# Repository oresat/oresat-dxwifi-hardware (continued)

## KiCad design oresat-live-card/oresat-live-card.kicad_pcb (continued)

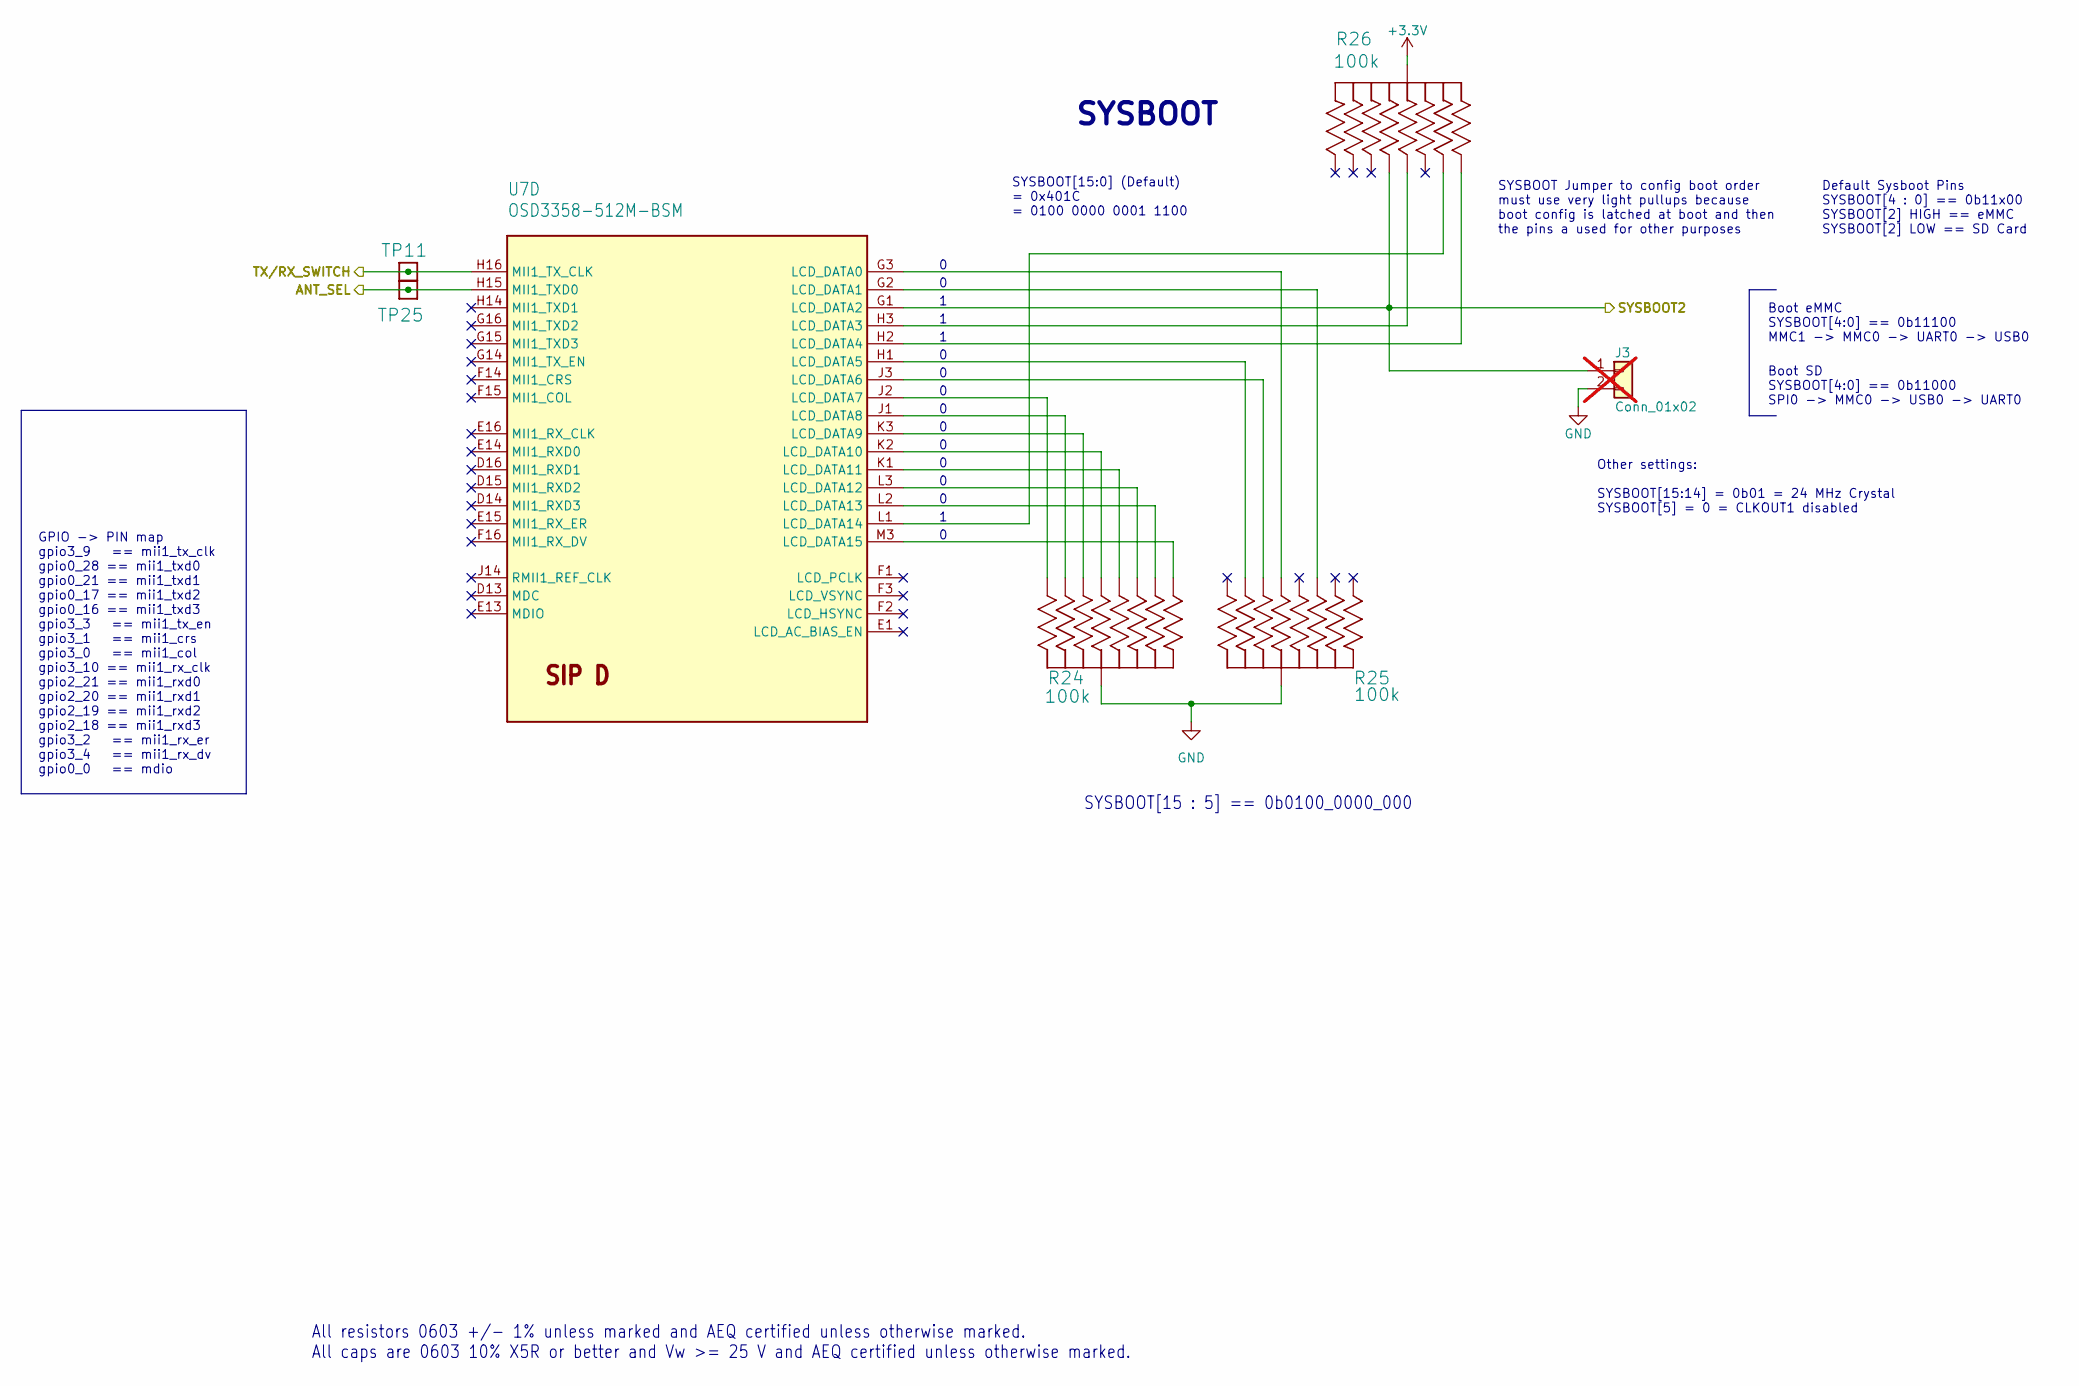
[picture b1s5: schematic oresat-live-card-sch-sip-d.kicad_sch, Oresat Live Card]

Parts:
J3: Conn_01x02; PinHeader_1x02_P2.54mm_Vertical; not fitted
R24, R25, R26: 100k; ARRAY_EXBA-M; MPN EXB-A10P104J
TP11, TP25: TEST-POINT3X4; TestPoint_Pad_D1.0mm
U7: OSD3358-512M-BSM; U-Octavo-OSD335X-BGA-256; MPN OSD3358-512M-BSM

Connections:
+3.3V: R26.5 (55), R26.10 (55); also elsewhere on the board
/Power + OPD/SYSBOOT2: J3.1, R26.8 (88), U7.G1 (LCD_DATA2); also elsewhere on the board
/SIP D: Boot/ANT_SEL: TP25.1 (1_1), U7.H15 (MII1_TXD0); also elsewhere on the board
/SIP D: Boot/TX/RX_SWITCH: TP11.1 (1_1), U7.H16 (MII1_TX_CLK); also elsewhere on the board
GND: J3.2, R24.5 (55), R24.10 (55), R25.5 (55), R25.10 (55); also elsewhere on the board
unnamed: R24.1 (11), U7.M3 (LCD_DATA15)
unnamed: R24.2 (22), U7.L3 (LCD_DATA12)
unnamed: R24.3 (33), U7.K2 (LCD_DATA10)
unnamed: R24.4 (44), U7.J1 (LCD_DATA8)
unnamed: R24.6 (66), U7.J2 (LCD_DATA7)
unnamed: R24.7 (77), U7.K3 (LCD_DATA9)
unnamed: R24.8 (88), U7.K1 (LCD_DATA11)
unnamed: R24.9 (99), U7.L2 (LCD_DATA13)
unnamed: R25.2 (22), U7.G2 (LCD_DATA1)
unnamed: R25.3 (33), U7.G3 (LCD_DATA0)
unnamed: R25.4 (44), U7.H1 (LCD_DATA5)
unnamed: R25.7 (77), U7.J3 (LCD_DATA6)
unnamed: R26.3 (33), U7.H3 (LCD_DATA3)
unnamed: R26.4 (44), U7.L1 (LCD_DATA14)
unnamed: R26.6 (66), U7.H2 (LCD_DATA4)

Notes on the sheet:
All resistors 0603 +/- 1% unless marked and AEQ certified unless otherwise marked. All caps are 0603 10% X5R or better and Vw >= 25 V and AEQ certified unless otherwise marked.
Boot eMMC SYSBOOT[4:0] == 0b11100 MMC1 -> MMC0 -> UART0 -> USB0
GPIO -> PIN map gpio3_9 == mii1_tx_clk gpio0_28 == mii1_txd0 gpio0_21 == mii1_txd1 gpio0_17 == mii1_txd2 gpio0_16 == mii1_txd3 gpio3_3 == mii1_tx_en gpio3_1 == mii1_crs gpio3_0 == mii1_col gpio3_10 == mii1_rx_clk gpio2_21 == mii1_rxd0 gpio2_20 == mii1_rxd1 gpio2_19 == mii1_rxd2 gpio2_18 == mii1_rxd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
Boot SD SYSBOOT[4:0] == 0b11000 SPI0 -> MMC0 -> USB0 -> UART0
SYSBOOT[15 : 5] == 0b0100_0000_000
SYSBOOT Jumper to config boot order must use very light pullups because boot config is latched at boot and then the pins a used for other purposes
Other settings: SYSBOOT[15:14] = 0b01 = 24 MHz Crystal SYSBOOT[5] = 0 = CLKOUT1 disabled
SYSBOOT
Default Sysboot Pins SYSBOOT[4 : 0] == 0b11x00 SYSBOOT[2] HIGH == eMMC SYSBOOT[2] LOW == SD Card
SYSBOOT[15:0] (Default) = 0x401C = 0100 0000 0001 1100

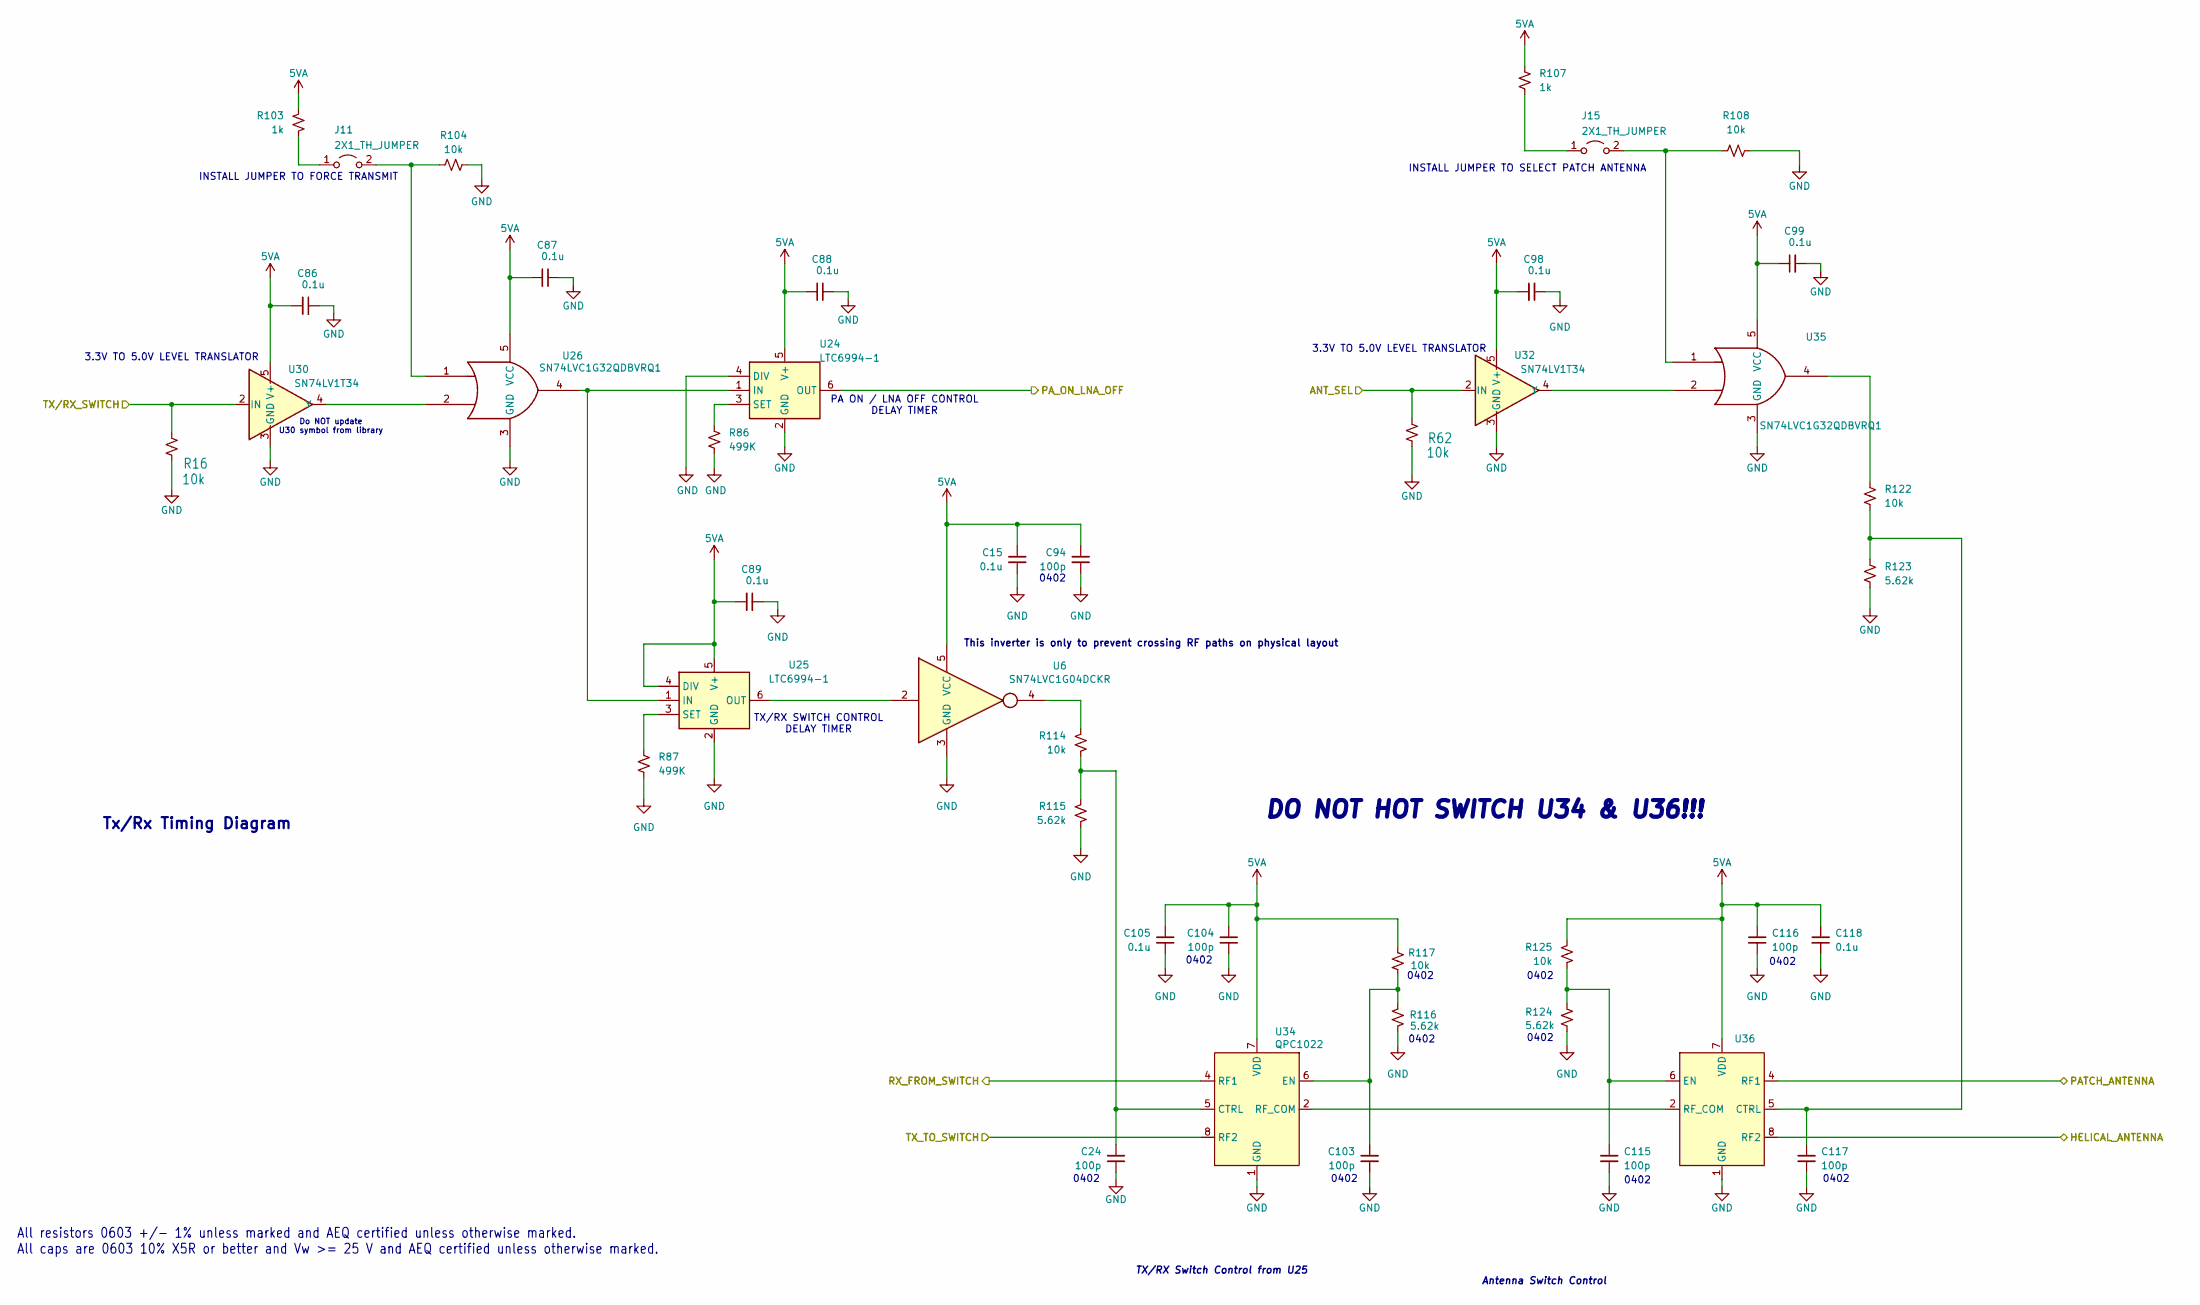
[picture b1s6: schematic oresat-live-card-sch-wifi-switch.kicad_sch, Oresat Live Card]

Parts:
C15, C86, C87, C88, C89, C98, C99, C105, C118: 0.1u; 0603-C-NOSILK; MPN C0603C104K5RACAUTO
C24, C94, C103, C104, C115, C116, C117: 100p; 0402-C-NOSILK; MPN GCM1555C1H101GA16D
J11, J15: 2X1_TH_JUMPER; 2X1; MPN XGL4020-332MEC
R16, R62, R104, R108, R114, R122: 10k; 0603-C-NOSILK; MPN RMCF0603FT10K0
R86, R87: 499K; 0603-C-NOSILK; MPN RMCF0603FT499K
R103, R107: 1k; 0603-C-NOSILK; MPN RMCF0603FT1K00
R115, R123: 5.62k; 0603-C-NOSILK; MPN RMCF0603FT5K62
R116, R124: 5.62k; 0402-C-NOSILK; MPN RMCF0402FT5K62
R117, R125: 10k; 0402-C-NOSILK; MPN RMCF0402FT10K0
U6: SN74LVC1G04DCKR; C70(TI-DCK); MPN SN74LVC1G04DCKR
U24, U25: LTC6994-1; TSOT-23-6; MPN LTC6994IS6-1#TRPBF
U26, U35: SN74LVC1G32QDBVRQ1; SOT-23-5; MPN SN74LVC1G32QDBVRQ1
U30, U32: SN74LV1T34; SOT-353_SC-70-5; MPN SN74LV1T34QDCKRQ1
U34, U36: QPC1022; MPN QPC1022TR7

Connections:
5VA: C15.1, C86.1, C87.1, C88.1, C89.1, C94.1, C98.1, C99.1, C104.1, C105.1, C116.1, C118.1, R103.1, R107.1, R117.1, R125.2, U6.5 (VCC), U24.5 (V+), U25.4 (DIV), U25.5 (V+), U26.5 (VCC), U30.5 (V+), U32.5 (V+), U34.7 (VDD), U35.5 (VCC), U36.7 (VDD); also elsewhere on the board
/HEL_ANT: U36.8 (RF2); also elsewhere on the board
/PATCH_ANT: U36.4 (RF1); also elsewhere on the board
/SIP D: Boot/ANT_SEL: R62.2, U32.2 (IN); also elsewhere on the board
/SIP D: Boot/TX/RX_SWITCH: R16.2, U30.2 (IN); also elsewhere on the board
/WiFi LNA/LNA_SHUTDOWN: U24.6 (OUT); also elsewhere on the board
/WiFi LNA/RX_FROM_SWITCH: U34.4 (RF1); also elsewhere on the board
/WiFi PA/TX_TO_SWITCH: U34.8 (RF2); also elsewhere on the board
GND: C15.2, C24.2, C86.2, C87.2, C88.2, C89.2, C94.2, C98.2, C99.2, C103.2, C104.2, C105.2, C115.2, C116.2, C117.2, C118.2, R16.1, R62.1, R86.2, R87.2, R104.2, R108.2, R115.2, R116.2, R123.1, R124.1, U6.3 (GND), U24.2 (GND), U24.4 (DIV), U25.2 (GND), U26.3 (GND), U30.3 (GND), U32.3 (GND), U34.1 (GND), U34.3 (GND), U34.9 (GND), U35.3 (GND), U36.1 (GND), U36.3 (GND), U36.9 (GND); also elsewhere on the board
unnamed: J11.1 (A), R103.2
unnamed: J11.2 (B), R104.1, U26.1
unnamed: J15.1 (A), R107.2
unnamed: J15.2 (B), R108.1, U35.1
unnamed: R114.2, U6.4
unnamed: R122.1, U35.4
unnamed: U24.1 (IN), U25.1 (IN), U26.4
unnamed: R86.1, U24.3 (SET)
unnamed: U6.2, U25.6 (OUT)
unnamed: R87.1, U25.3 (SET)
unnamed: U26.2, U30.4 (Y)
unnamed: U32.4 (Y), U35.2
unnamed: C24.1, R114.1, R115.1, U34.5 (CTRL)
unnamed: C103.1, R116.1, R117.2, U34.6 (EN)
unnamed: U34.2 (RF_COM), U36.2 (RF_COM)
unnamed: C117.1, R122.2, R123.2, U36.5 (CTRL)
unnamed: C115.1, R124.2, R125.1, U36.6 (EN)

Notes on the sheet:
DO NOT HOT SWITCH U34 & U36!!!
3.3V TO 5.0V LEVEL TRANSLATOR
0402
This inverter is only to prevent crossing RF paths on physical layout
Tx/Rx Timing Diagram
INSTALL JUMPER TO SELECT PATCH ANTENNA
Do NOT update U30 symbol from library
TX/RX SWITCH CONTROL DELAY TIMER
All resistors 0603 +/- 1% unless marked and AEQ certified unless otherwise marked. All caps are 0603 10% X5R or better and Vw >= 25 V and AEQ certified unless otherwise marked.
Antenna Switch Control
PA ON / LNA OFF CONTROL DELAY TIMER
INSTALL JUMPER TO FORCE TRANSMIT
3.3V TO 5.0V LEVEL TRANSLATOR
TX/RX Switch Control from U25

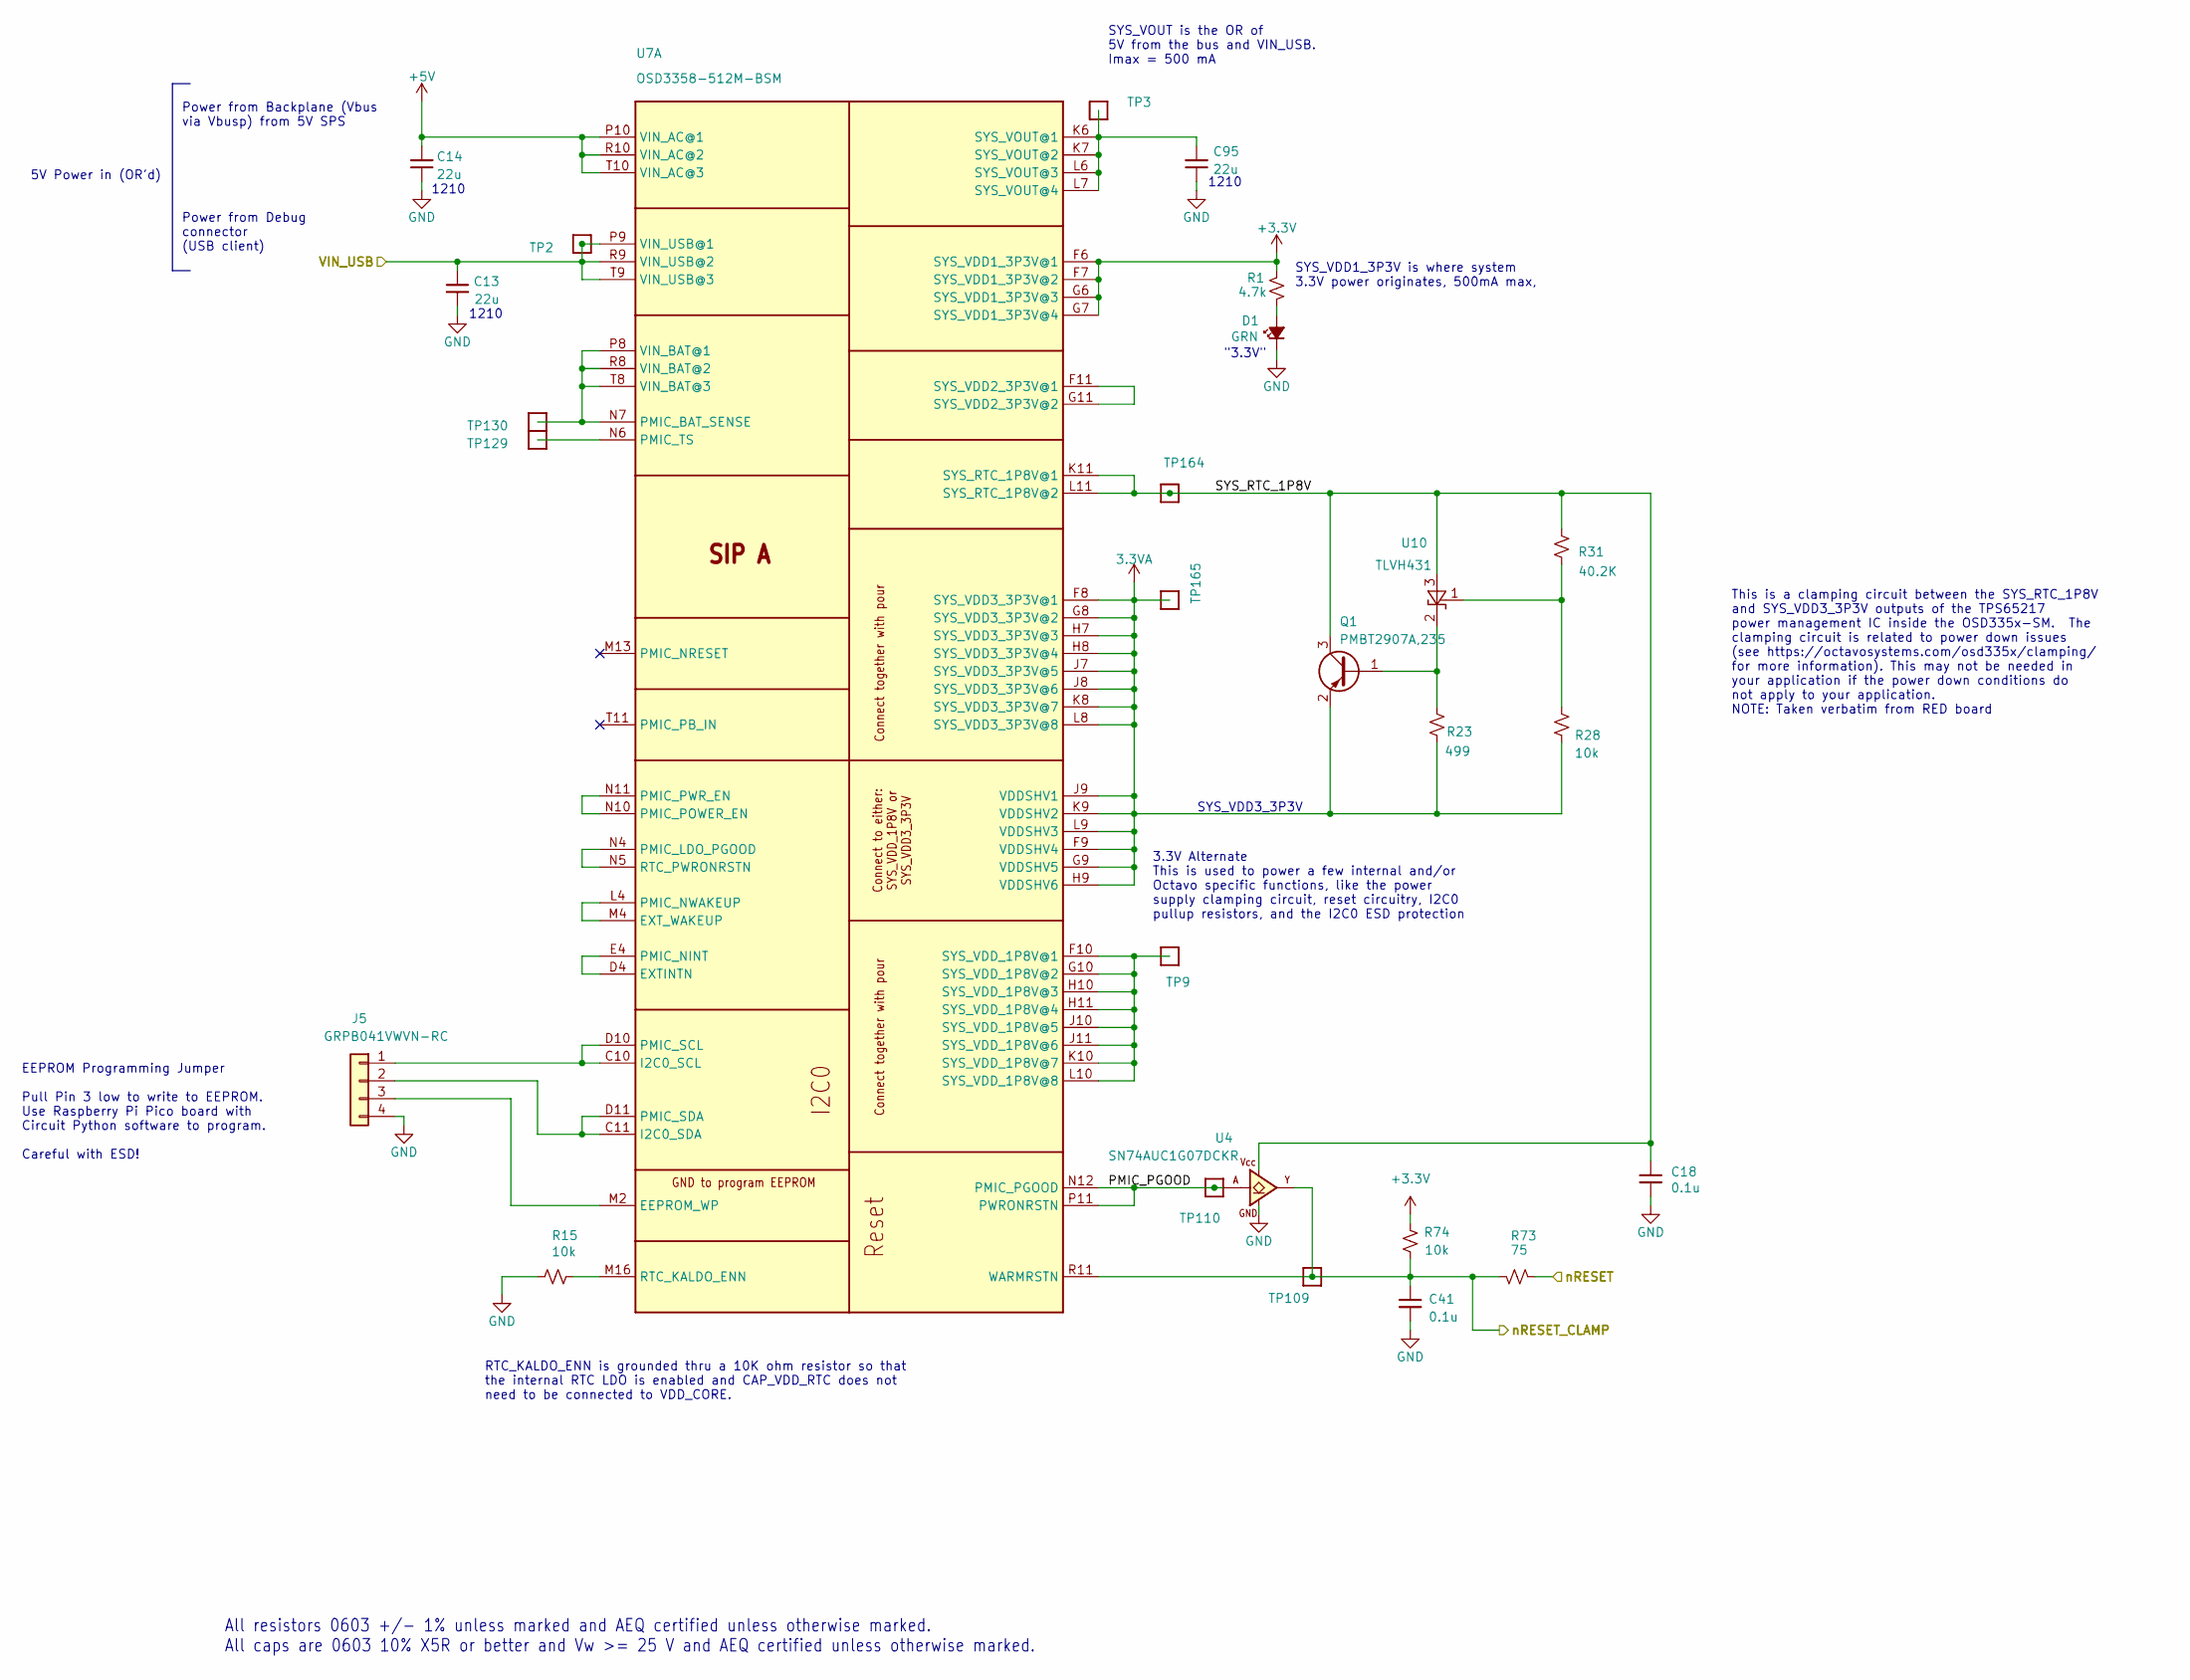
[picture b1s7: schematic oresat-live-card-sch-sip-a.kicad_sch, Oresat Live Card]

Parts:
C13, C14, C95: 22u; C_1210_3225Metric; MPN TMK325B7226KMHP
C18, C41: 0.1u; 0603-C-NOSILK; MPN C0603C104K5RACAUTO
D1: GRN; LED-0603; MPN 150060GS75000
J5: GRPB041VWVN-RC; PinHeader_1x04_P1.27mm_Vertical; MPN GRPB041VWVN-RC
Q1: PMBT2907A,235; SOT-23; MPN PMBT2907A,235
R1: 4.7k; 0603-C-NOSILK; MPN RMCF0603FT4K70
R15, R28, R74: 10k; 0603-C-NOSILK; MPN RMCF0603FT10K0
R23: 499; 0603-C-NOSILK; MPN RMCF0603FT499R
R31: 40.2K; 0603-C-NOSILK; MPN RMCF0603FG40K2
R73: 75; 0603-C-NOSILK; MPN RMCF0603FT75R0
TP2, TP3, TP9, TP109, TP110, TP129, TP130, TP164, TP165: TEST-POINT3X4; TestPoint_Pad_D1.0mm
U4: SN74AUC1G07DCKR; C70(TI-DCK); MPN SN74AUC1G07DCKR
U7: OSD3358-512M-BSM; U-Octavo-OSD335X-BGA-256; MPN OSD3358-512M-BSM
U10: TLVH431; SOT23-3; MPN TLVH431BQDBZRQ1

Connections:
3.3VA: Q1.2 (E), R23.2, R28.2, TP165.1 (1_1), U7.F8 (SYS_VDD3_3P3V@1), U7.F9 (VDDSHV4), U7.G8 (SYS_VDD3_3P3V@2), U7.G9 (VDDSHV5), U7.H7 (SYS_VDD3_3P3V@3), U7.H8 (SYS_VDD3_3P3V@4), U7.H9 (VDDSHV6), U7.J7 (SYS_VDD3_3P3V@5), U7.J8 (SYS_VDD3_3P3V@6), U7.J9 (VDDSHV1), U7.K8 (SYS_VDD3_3P3V@7), U7.K9 (VDDSHV2), U7.L8 (SYS_VDD3_3P3V@8), U7.L9 (VDDSHV3)
+3.3V: R1.1, R74.2, U7.F6 (SYS_VDD1_3P3V@1), U7.F7 (SYS_VDD1_3P3V@2), U7.G6 (SYS_VDD1_3P3V@3), U7.G7 (SYS_VDD1_3P3V@4); also elsewhere on the board
+5V: C14.1, U7.P10 (VIN_AC@1), U7.R10 (VIN_AC@2), U7.T10 (VIN_AC@3); also elsewhere on the board
/SIP A: Power/PMIC_PGOOD: TP110.1 (1_1), U4.2 (A), U7.N12 (PMIC_PGOOD), U7.P11 (PWRONRSTN)
/SIP A: Power/SYS_RTC_1P8V: C18.1, Q1.3 (C), R31.1, TP164.1 (1_1), U4.5 (VCC), U7.K11 (SYS_RTC_1P8V@1), U7.L11 (SYS_RTC_1P8V@2), U10.3 (A)
/SIP A: Power/VIN_USB: C13.1, TP2.1 (1_1), U7.P9 (VIN_USB@1), U7.R9 (VIN_USB@2), U7.T9 (VIN_USB@3); also elsewhere on the board
/SIP A: Power/nRESET_CLAMP: C41.1, R73.2, R74.1, TP109.1 (1_1), U4.4 (Y), U7.R11 (WARMRSTN); also elsewhere on the board
/nRESET: R73.1; also elsewhere on the board
GND: C13.2, C14.2, C18.2, C41.2, C95.2, D1.1 (K), J5.4, R15.1, U4.3 (GND); also elsewhere on the board
unnamed: D1.2 (A), R1.2
unnamed: J5.1, U7.C10 (I2C0_SCL), U7.D10 (PMIC_SCL)
unnamed: J5.2, U7.C11 (I2C0_SDA), U7.D11 (PMIC_SDA)
unnamed: J5.3, U7.M2 (EEPROM_WP)
unnamed: Q1.1 (B), R23.1, U10.2 (K)
unnamed: U7.D4 (EXTINTN), U7.E4 (PMIC_NINT)
unnamed: U7.L4 (PMIC_NWAKEUP), U7.M4 (EXT_WAKEUP)
unnamed: TP130.1 (1_1), U7.N7 (PMIC_BAT_SENSE), U7.P8 (VIN_BAT@1), U7.R8 (VIN_BAT@2), U7.T8 (VIN_BAT@3)
unnamed: U7.N4 (PMIC_LDO_PGOOD), U7.N5 (RTC_PWRONRSTN)
unnamed: U7.N10 (PMIC_POWER_EN), U7.N11 (PMIC_PWR_EN)
unnamed: TP129.1 (1_1), U7.N6 (PMIC_TS)
unnamed: R15.2, U7.M16 (RTC_KALDO_ENN)
unnamed: U7.F11 (SYS_VDD2_3P3V@1), U7.G11 (SYS_VDD2_3P3V@2)
unnamed: TP9.1 (1_1), U7.F10 (SYS_VDD_1P8V@1), U7.G10 (SYS_VDD_1P8V@2), U7.H10 (SYS_VDD_1P8V@3), U7.H11 (SYS_VDD_1P8V@4), U7.J10 (SYS_VDD_1P8V@5), U7.J11 (SYS_VDD_1P8V@6), U7.K10 (SYS_VDD_1P8V@7), U7.L10 (SYS_VDD_1P8V@8)
unnamed: C95.1, TP3.1 (1_1), U7.K6 (SYS_VOUT@1), U7.K7 (SYS_VOUT@2), U7.L6 (SYS_VOUT@3), U7.L7 (SYS_VOUT@4)
unnamed: R28.1, R31.2, U10.1 (REF)

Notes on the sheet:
Power from Backplane (Vbus via Vbusp) from 5V SPS
All resistors 0603 +/- 1% unless marked and AEQ certified unless otherwise marked. All caps are 0603 10% X5R or better and Vw >= 25 V and AEQ certified unless otherwise marked.
SYS_VOUT is the OR of 5V from the bus and VIN_USB. Imax = 500 mA
EEPROM Programming Jumper Pull Pin 3 low to write to EEPROM. Use Raspberry Pi Pico board with Circuit Python software to program. Careful with ESD!
"3.3V"
5V Power in (OR'd)
RTC_KALDO_ENN is grounded thru a 10K ohm resistor so that the internal RTC LDO is enabled and CAP_VDD_RTC does not need to be connected to VDD_CORE.
SYS_VDD1_3P3V is where system 3.3V power originates, 500mA max,
Power from Debug connector (USB client)
This is a clamping circuit between the SYS_RTC_1P8V and SYS_VDD3_3P3V outputs of the TPS65217 power management IC inside the OSD335x-SM. The clamping circuit is related to power down issues (see https://octavosystems.com/osd335x/clamping/ for more information). This may not be needed in your applic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
1210
SYS_VDD3_3P3V
3.3V Alternate This is used to power a few internal and/or Octavo specific functions, like the power supply clamping circuit, reset circuitry, I2C0 pullup resistors, and the I2C0 ESD protection

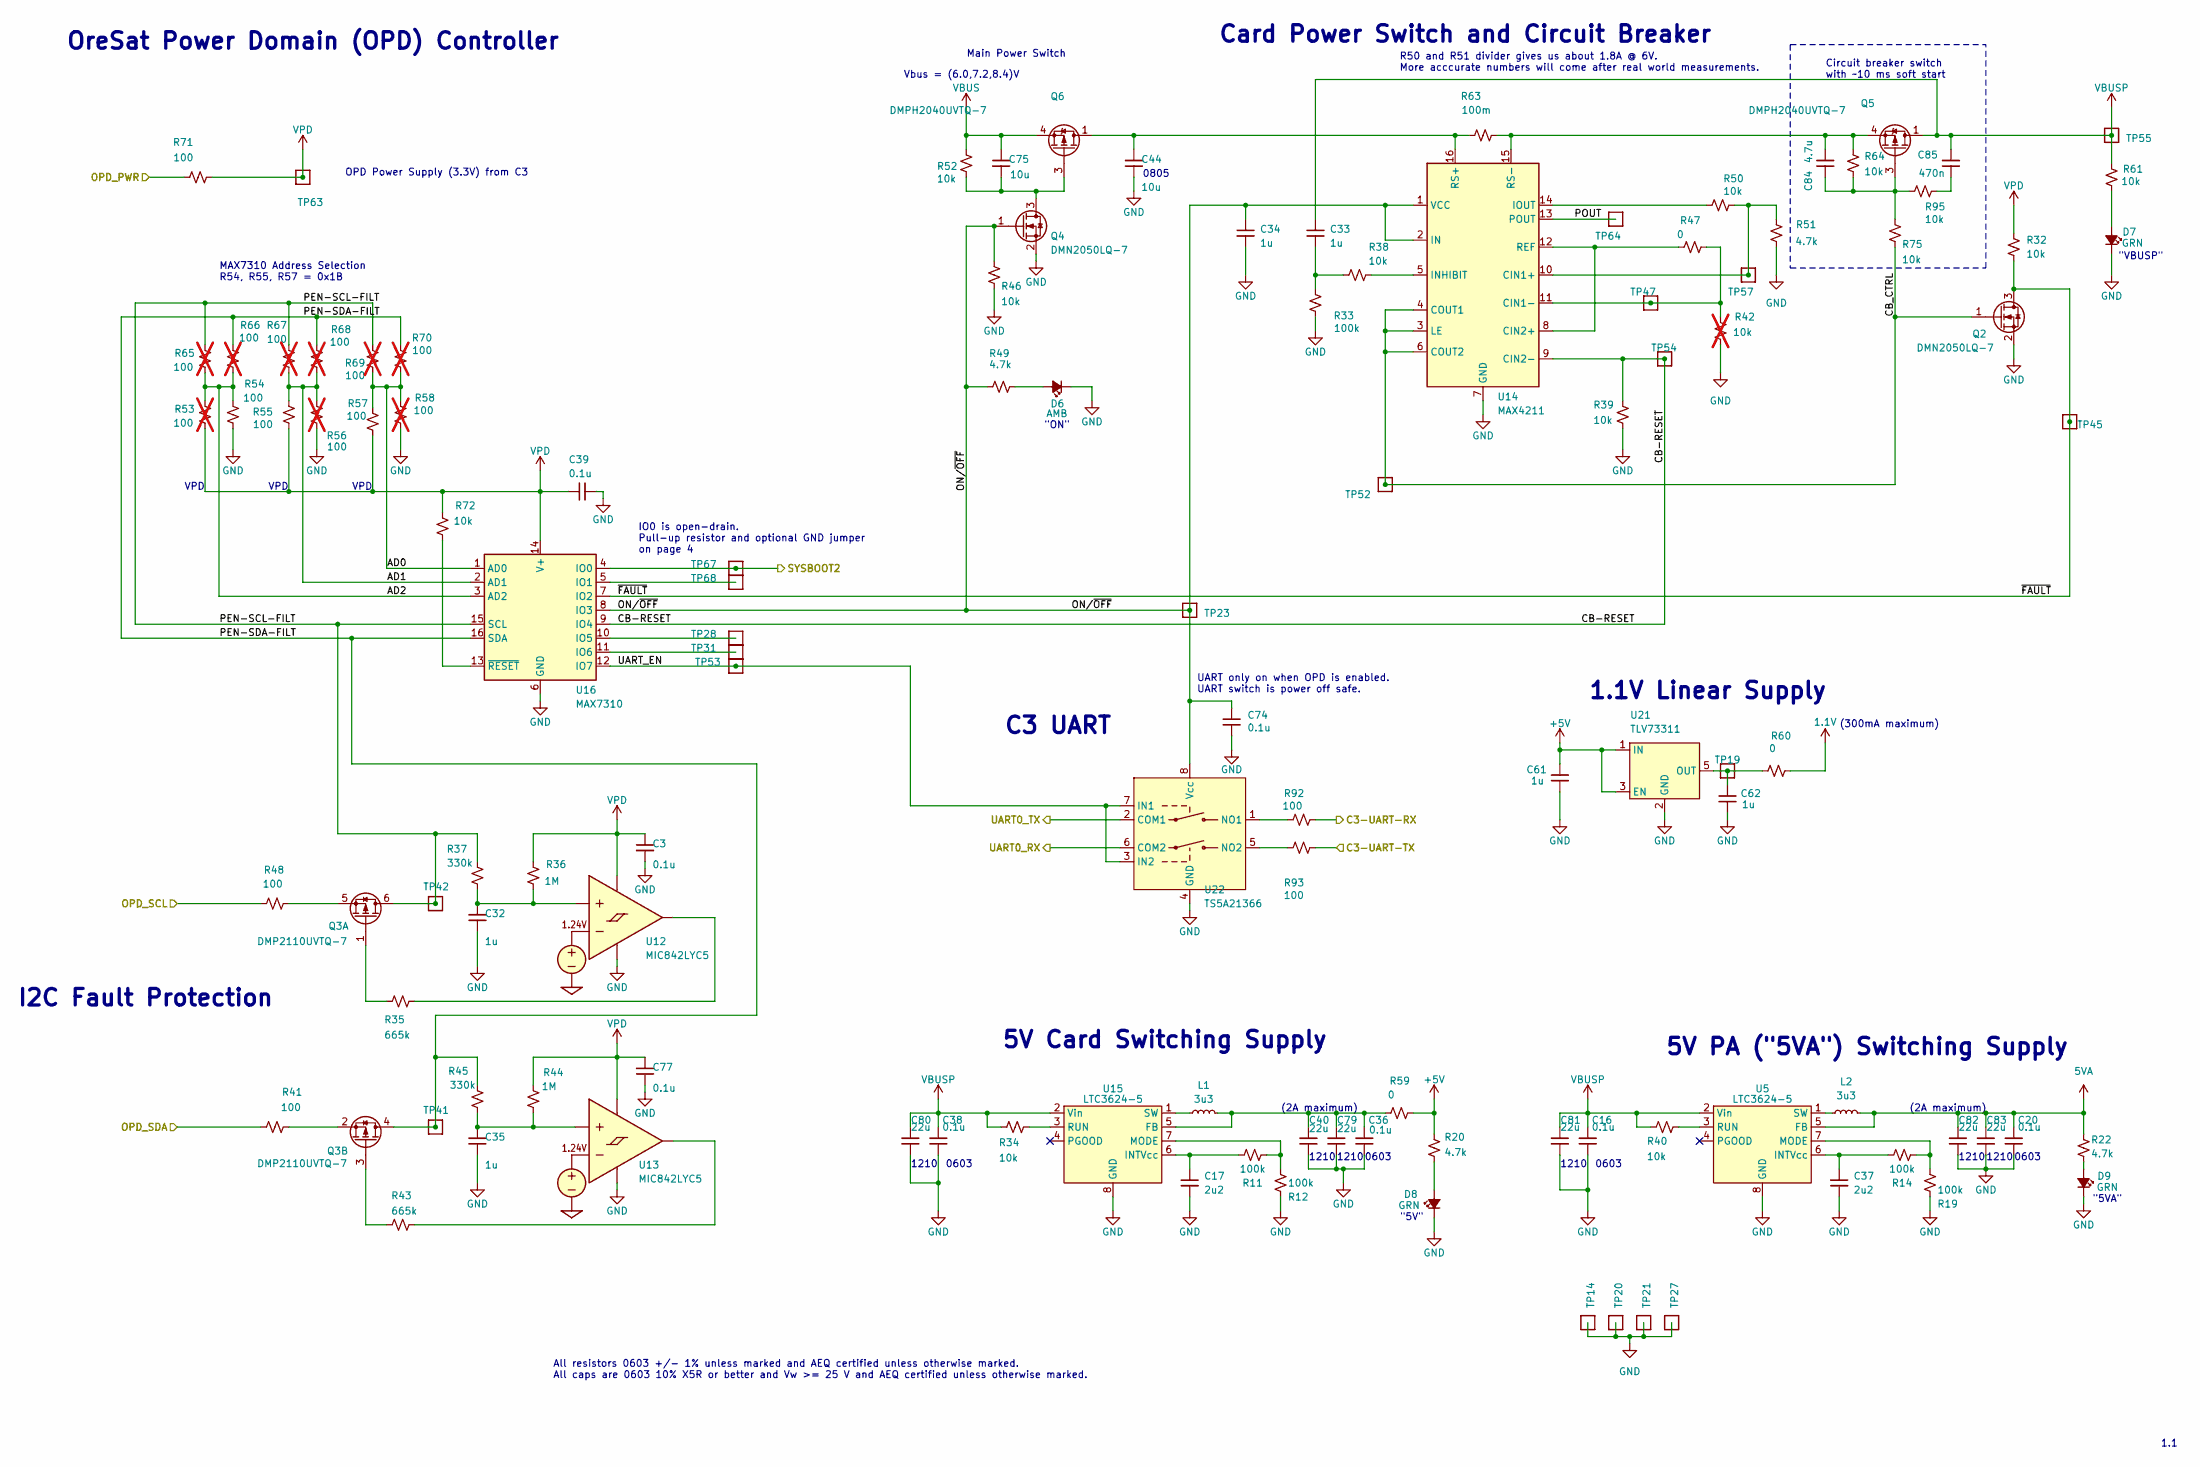
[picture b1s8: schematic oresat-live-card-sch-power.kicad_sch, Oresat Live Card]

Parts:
C3, C16, C20, C36, C38, C39, C74, C77: 0.1u; 0603-C-NOSILK; MPN C0603C104K5RACAUTO
C17, C37: 2u2; 0603-C-NOSILK; MPN GRT188C71E225KE13D
C32, C35: 1u; 0805-C-NOSILK; MPN GCM21BR71H105KA03L
C33, C34, C61, C62: 1u; 0603-C-NOSILK; MPN GRT188R71E105KE13D
C40, C79, C80, C81, C82, C83: 22u; C_1210_3225Metric; MPN TMK325B7226KMHP
C44, C75: 10u; 0805-C-NOSILK; MPN GRT21BC71E106KE13K
C84: 4.7u; 0805-C-NOSILK; MPN GRT21BC71E475KE13L
C85: 470n; 0603-C-NOSILK; MPN C0603C474K3RACAUTO
D6: AMB; LED-0603; MPN 150060AS75000
D7, D8, D9: GRN; LED-0603; MPN 150060GS75000
L1, L2: 3u3; L_Coilcraft_XxL4020; MPN XGL4020-332MEC
Q2, Q4: DMN2050LQ-7; SOT-23; MPN DMN2050LQ-7
Q3: DMP2110UVTQ-7; SOT-23-6; MPN DMP2110UVTQ-7
Q5, Q6: DMPH2040UVTQ-7; TSOT-23-6; MPN DMPH2040UVTQ-7
R11, R12, R14, R19, R33: 100k; 0603-C-NOSILK; MPN RMCF0603FT100K
R20, R22, R49, R51: 4.7k; 0603-C-NOSILK; MPN RMCF0603FT4K70
R32, R34, R38, R39, R40, R46, R50, R52, R61, R64, R72, R75, R95: 10k; 0603-C-NOSILK; MPN RMCF0603FT10K0
R35, R43: 665k; 0603-C-NOSILK; MPN RMCF0603FT665K
R36, R44: 1M; 0603-C-NOSILK; MPN RMCF0603FT1M00
R37, R45: 330k; 0603-C-NOSILK; MPN RMCF0603FT330K
R41, R48, R54, R55, R57, R71, R92, R93: 100; 0603-C-NOSILK; MPN RMCF0603FT100R
R42: 10k; R_0603_1608Metric; MPN ERJ-3EKF1002V; not fitted
R47, R59, R60: 0; 0603-C-NOSILK; MPN RMCF0603ZT0R00
R53, R56, R58, R65, R66, R67, R68, R69, R70: 100; 0603-C-NOSILK; MPN ERJ-3EKF1000V; not fitted
R63: 100m; 1206-C; MPN CSR1206FKR100
TP14, TP20, TP21, TP27, TP55: TEST-POINT; TestPoint-0.75mm-th
TP19, TP23, TP28, TP31, TP41, TP42, TP45, TP47, TP52, TP53, TP54, TP57, TP63, TP64, TP67, TP68: TEST-POINT; TestPoint_Pad_D1.0mm
U5, U15: LTC3624-5; DFN-8-1EP_3x3mm_P0.5mm_EP1.65x2.38mm_ThermalVias0.3mm; MPN LTC3624IDD-5#PBF
U12, U13: MIC842LYC5; SOT-353_SC-70-5; MPN MIC842LYC5-TR
U14: MAX4211; QFN-16-1EP_4x4mm_P0.65mm_EP2.1x2.1mm; MPN MAX4211FETE+
U16: MAX7310; QFN-16-1EP_4x4mm_P0.65mm_EP2.1x2.1mm; MPN MAX7310ATE+
U21: TLV73311; SOT-23-5; MPN TLV73311PDBVR
U22: TS5A21366; VSSOP-8_2.3x2mm_P0.5mm; MPN TS5A21366DCUR

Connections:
1.1V: R60.2; also elsewhere on the board
5VA: C20.1, C82.1, C83.1, L2.2, R22.1, U5.5 (FB); also elsewhere on the board
+5V: C61.1, R20.1, R59.2, U21.1 (IN), U21.3 (EN); also elsewhere on the board
/C3-UART-RX: R92.1; also elsewhere on the board
/C3-UART-TX: R93.1; also elsewhere on the board
/OPD_PWR: R71.1; also elsewhere on the board
/OPD_SCL: R48.1; also elsewhere on the board
/OPD_SDA: R41.1; also elsewhere on the board
/Power + OPD/AD0: R57.1, R58.2, R69.2, R70.1, U16.1 (AD0)
/Power + OPD/AD1: R55.1, R56.2, R67.2, R68.1, U16.2 (AD1)
/Power + OPD/AD2: R53.1, R54.2, R65.2, R66.1, U16.3 (AD2)
/Power + OPD/CB-RESET: R39.2, TP54.1 (1_1), U14.9 (CIN2-), U16.9 (IO4)
/Power + OPD/CB_CTRL: Q2.1 (G), R75.1, TP52.1 (1_1), U14.3 (LE), U14.4 (COUT1), U14.6 (COUT2)
/Power + OPD/ON/~OFF: C34.1, C74.1, Q4.1 (G), R46.2, R49.2, TP23.1 (1_1), U14.1 (VCC), U14.2 (IN), U16.8 (IO3), U22.8 (Vcc)
/Power + OPD/PEN-SCL-FILT: Q3.6 (D), R37.2, R65.1, R67.1, R69.1, TP42.1 (1_1), U16.15 (SCL)
/Power + OPD/PEN-SDA-FILT: Q3.4 (D), R45.2, R66.2, R68.2, R70.2, TP41.1 (1_1), U16.16 (SDA)
/Power + OPD/POUT: TP64.1 (1_1), U14.13 (POUT)
/Power + OPD/SYSBOOT2: TP67.1 (1_1), U16.4 (IO0); also elsewhere on the board
/Power + OPD/UART_EN: TP53.1 (1_1), U16.12 (IO7), U22.3 (IN2), U22.7 (IN1)
/Power + OPD/~FAULT: Q2.3 (D), R32.1, TP45.1 (1_1), U16.7 (IO2)
/UART0_RX: U22.6 (COM2); also elsewhere on the board
/UART0_TX: U22.2 (COM1); also elsewhere on the board
GND: C3.2, C16.2, C17.2, C20.2, C32.2, C34.2, C35.2, C36.2, C37.2, C38.2, C39.1, C40.2, C44.2, C61.2, C62.2, C74.2, C77.2, C79.2, C80.2, C81.2, C82.2, C83.2, D6.1 (K), D7.1 (K), D8.1 (K), D9.1 (K), Q2.2 (S), Q4.2 (S), R12.2, R19.2, R33.1, R39.1, R42.1, R46.1, R51.1, R54.1, R56.1, R58.1, TP14.1 (1_1), TP20.1 (1_1), TP21.1 (1_1), TP27.1 (1_1), U5.8 (GND), U5.9 (GND), U12.2 (GND), U13.2 (GND), U14.7 (GND), U14.17 (GND), U15.8 (GND), U15.9 (GND), U16.6 (GND), U16.17 (GND), U21.2 (GND), U22.4 (GND); also elsewhere on the board
unnamed: C33.1, R33.2, R38.2
unnamed: C85.2, R95.1
unnamed: D6.2 (A), R49.1
unnamed: D7.2 (A), R61.1
unnamed: D8.2 (A), R20.2
unnamed: D9.2 (A), R22.2
unnamed: Q3.1 (G), R35.2
unnamed: Q3.5 (S), R48.2
unnamed: Q3.3 (G), R43.2
unnamed: Q3.2 (S), R41.2
unnamed: C75.2, Q4.3 (D), Q6.3 (G), R52.1
unnamed: C84.1, Q5.3 (G), R64.1, R75.2, R95.2
unnamed: C84.2, Q5.4 (S), R63.2, R64.2, U14.15 (RS-)
unnamed: C37.1, R14.1, U5.6 (INTVcc)
unnamed: R14.2, R19.1, U5.7 (MODE)
unnamed: R40.1, U5.3 (RUN)
unnamed: L2.1, U5.1 (SW)
unnamed: C32.1, R36.1, R37.1, U12.1 (INP)
unnamed: R35.1, U12.4 (OUT)
unnamed: C35.1, R44.1, R45.1, U13.1 (INP)
unnamed: R43.1, U13.4 (OUT)
unnamed: R50.2, R51.2, TP57.1 (1_1), U14.10 (CIN1+)
unnamed: R42.2, R47.1, TP47.1 (1_1), U14.11 (CIN1-)
unnamed: R47.2, U14.8 (CIN2+), U14.12 (REF)
unnamed: R38.1, U14.5 (INHIBIT)
unnamed: R50.1, U14.14 (IOUT)
unnamed: C44.1, Q6.1 (D), Q6.2 (D), Q6.5 (D), Q6.6 (D), R63.1, U14.16 (RS+)
unnamed: C36.1, C40.1, C79.1, L1.2, R59.1, U15.5 (FB)
unnamed: C17.1, R11.1, U15.6 (INTVcc)
unnamed: R11.2, R12.1, U15.7 (MODE)
unnamed: R34.1, U15.3 (RUN)
unnamed: L1.1, U15.1 (SW)
unnamed: TP68.1 (1_1), U16.5 (IO1)
unnamed: TP28.1 (1_1), U16.10 (IO5)
unnamed: TP31.1 (1_1), U16.11 (IO6)
unnamed: R72.1, U16.13 (~RESET)
unnamed: C62.1, R60.1, TP19.1 (1_1), U21.5 (OUT)
unnamed: R92.2, U22.1 (NO1)
unnamed: R93.2, U22.5 (NO2)
VBUS: C75.1, Q6.4 (S), R52.2; also elsewhere on the board
VBUSP: C16.1, C33.2, C38.1, C80.1, C81.1, C85.1, Q5.1 (D), Q5.2 (D), Q5.5 (D), Q5.6 (D), R34.2, R40.2, R61.2, TP55.1 (1_1), U5.2 (Vin), U15.2 (Vin)
VPD: C3.1, C39.2, C77.1, R32.2, R36.2, R44.2, R53.2, R55.2, R57.2, R71.2, R72.2, TP63.1 (1_1), U12.5 (VDD), U13.5 (VDD), U16.14 (V+)

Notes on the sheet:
1.1V Linear Supply
"5VA"
(300mA maximum)
(2A maximum)
1210
"VBUSP"
Circuit breaker switch with ~10 ms soft start
VPD
R50 and R51 divider gives us about 1.8A @ 6V. More acccurate numbers will come after real world measurements.
I2C Fault Protection
0603
5V PA ("5VA") Switching Supply
C3 UART
All resistors 0603 +/- 1% unless marked and AEQ certified unless otherwise marked. All caps are 0603 10% X5R or better and Vw >= 25 V and AEQ certified unless otherwise marked.
UART only on when OPD is enabled. UART switch is power off safe.
0805
1.1
Card Power Switch and Circuit Breaker
MAX7310 Address Selection R54, R55, R57 = 0x1B
"5V"
OPD Power Supply (3.3V) from C3
IO0 is open-drain. Pull-up resistor and optional GND jumper on page 4
Vbus = (6.0,7.2,8.4)V
OreSat Power Domain (OPD) Controller
5V Card Switching Supply
Main Power Switch
"ON"
